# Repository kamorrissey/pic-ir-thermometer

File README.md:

# pic-ir-thermometer

(Under construction.
Circuit schematic is stable; PCB design to be provided.
Firmware mostly complete but does not yet read from temperature sensor or read/write EEPROM.
3d-printable, handheld enclosure design to be provided.)

Open-source hardware and firmware for a PIC16LF19156-driven IR non-contact thermometer using a Melexis MLX90614 sensor and Lumex LCD-S401M16KR LCD segment display.

This project demonstrates several major functions of a Microchip PIC microcontroller (MCU):
1. using the built-in LCD driver module to directly drive a multiplexed LCD segment display
2. using the I2C/IIC/SMBus interface (MSSP) to communicate with an external temperature sensor
3. using the timer (TMR2, TMR4) and configurable logic cell (CLC) modules to debounce switch inputs in hardware
4. using the timer module (TMR0) to detect timeout of user input
5. using the internal voltage reference (FVR) and analog-to-digital converter (ADC) modules to detect low-battery state with no external components required
6. using the built-in EEPROM to read and write persistent data

The firmware is written in C using the free version of the Microchip MPLAB X IDE and XC8 compiler.
As much code as practical is generated rather than hand-written
by using the Microchip Code Configurator (MCC) plugin-in to MPLAB.
The full MPLAB project is provided.

The hardware uses minimal parts.
The surface mount MOSFET for battery protection is optional.
The full KiCad project containing schematic and PCB design is provided.

A 3D-printable, handheld enclosure design holding a single AA cell is provided.
All needed STL files for printing the enclosure are provided.

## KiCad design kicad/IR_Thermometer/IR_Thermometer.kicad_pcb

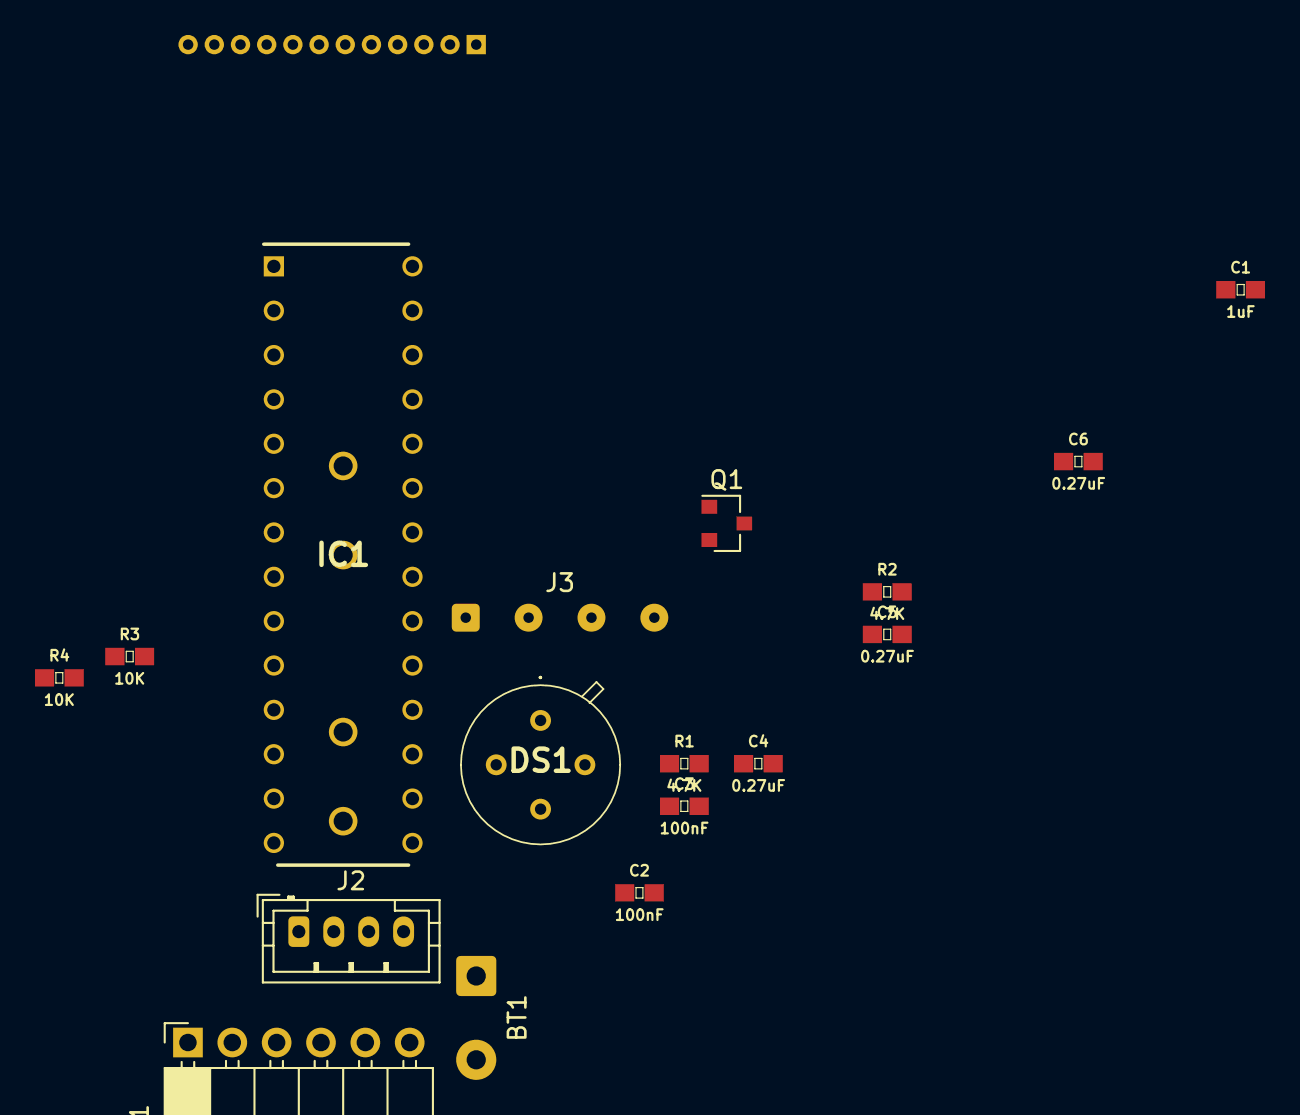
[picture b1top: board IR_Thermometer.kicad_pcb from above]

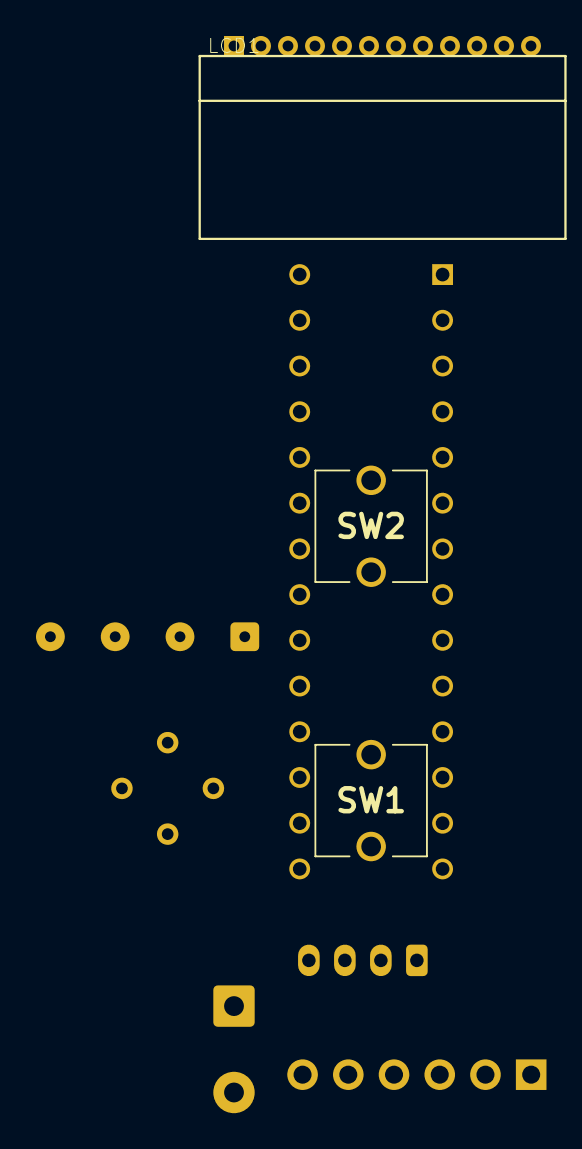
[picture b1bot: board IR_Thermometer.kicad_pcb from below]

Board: 4 copper layers, 20 parts (3 on the bottom side), 31 nets, no tracks yet.

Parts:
BT1: 3V; SolderWire-0.5sqmm_1x02_P4.8mm_D0.9mm_OD2.3mm
C1: 1uF; 0603
C2, C3: 100nF; 0603
C4, C5, C6: 0.27uF; 0603
DS1: MLX90614ESF-BAA; 1747
IC1: PIC16LF19156-I_SP; DIP794W56P254L3486H508Q28N
J1: ICSP Conn; PinSocket_1x06_P2.54mm_Horizontal
J2: Sensor Conn; JST_PH_B4B-PH-K_1x04_P2.00mm_Vertical
J3: Sensor Conn; SolderWire-0.1sqmm_1x04_P3.6mm_D0.4mm_OD1mm
LCD1: LCD-S401M16KR
Q1: SI2323; SOT-23
R1, R2: 4.7K; 0603
R3, R4: 10K; 0603
SW1: Option Button; FSM2JRT
SW2: Sample Button; FSM2JRT

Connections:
+3V0: C2.1, IC1.20, J1.2, J2.2, Q1.3, R3.1, R4.1
/I2C_SCL: IC1.14, J2.3
/I2C_SDA: IC1.15, J2.4
/ICSP_CLK: IC1.27, J1.5
/ICSP_DAT: IC1.28, J1.4
/ICSP_VPP: IC1.1, J1.1
/LCD_C0: IC1.25, LCD1.1
/LCD_C1: IC1.26, LCD1.2
/LCD_C2: IC1.13, LCD1.3
/LCD_C3: IC1.6, LCD1.4
/LCD_S0: IC1.10, LCD1.5
/LCD_S1: IC1.9, LCD1.6
/LCD_S2: IC1.5, LCD1.7
/LCD_S3: IC1.4, LCD1.8
/LCD_S4: IC1.3, LCD1.9
/LCD_S5: IC1.2, LCD1.10
/LCD_S6: IC1.22, LCD1.11
/LCD_S7: IC1.21, LCD1.12
GND: BT1.2, C2.2, C4.2, C5.2, C6.2, IC1.8, IC1.19, J1.3, J2.1, Q1.1, SW1.1, SW2.1
unnamed: BT1.1, Q1.2
unnamed: C1.1, IC1.24
unnamed: C1.2, IC1.23
unnamed: C3.1, DS1.3, J3.2, R1.1, R2.1
unnamed: C3.2, DS1.4, J3.1
unnamed: C4.1, IC1.16
unnamed: C5.1, IC1.17
unnamed: C6.1, IC1.18
unnamed: DS1.1, J3.3, R2.2
unnamed: DS1.2, J3.4, R1.2
unnamed: IC1.7, R4.2, SW2.2
unnamed: IC1.11, R3.2, SW1.2

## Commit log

2021-06-01 Update MEADME.md with image
2021-06-02 Fix units display and button handling
2021-06-02 Fix button2 release error
2021-06-02 Make input timeouts work
2021-06-17 Updates to schematic
2022-02-01 Read from MLX90614 sensor
2022-02-09 Implement MLX90614 sleep/wake
2022-03-12 Sleep mode implementation
